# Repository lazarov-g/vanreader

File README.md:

# vanreader
Van Protocol reader 
The source is for atmega328p ( arduino chip), and it's compiled in Atmel Studio ( IDE for atmel products).

These project purpouse is to connect existing Stalk controler on Peugeot 206 with Pioneer headunit, by listening the messages on the VAN network and sending signals to player.

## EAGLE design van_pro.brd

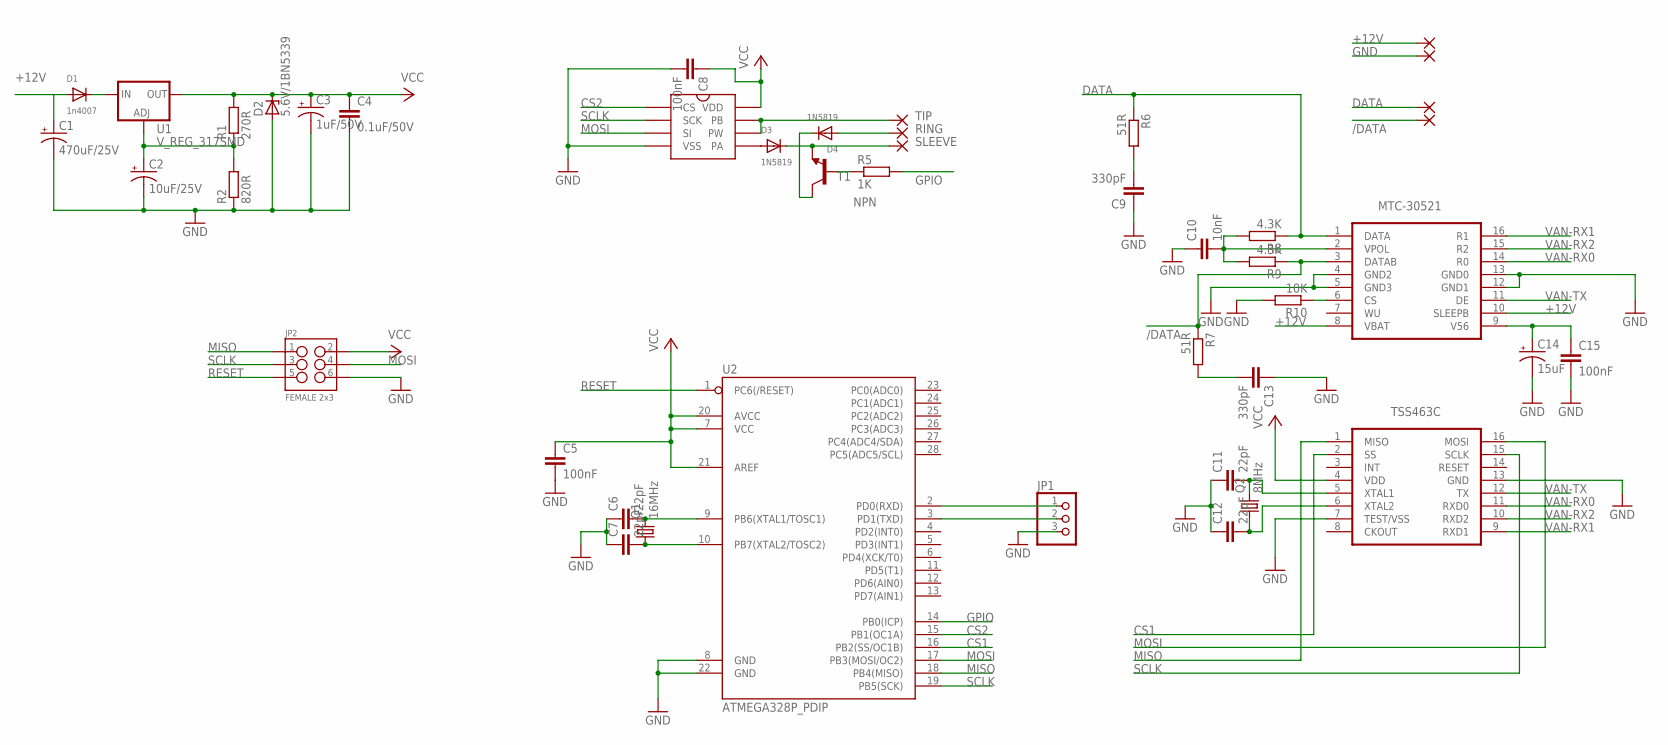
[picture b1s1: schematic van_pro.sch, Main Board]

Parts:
12V: WIREPAD2,54/0,8; 2,54/0,8
/DATA: WIREPAD2,54/0,8; 2,54/0,8
C1: 470uF/25V; E3,5-8
C2: 10uF/25V; E2-5
C3: 1uF/50V; E2-5
C4: 0.1uF/50V; C0805
C5, C8: 100nF; C0603
C6, C7, C11, C12: 22pF; C0603; MPN 08052A220JAT2A
C9, C13: 330pF; C0603; MPN 08052A220JAT2A
C10: 10nF; C0603; MPN 08052A220JAT2A
C14: 15uF; EIA3216; MPN 08052A220JAT2A
C15: 100nF; C1206; MPN 08052A220JAT2A
D1: 1n4007; SMADIODE
D2: 5.6V/1BN5339; DO41Z10
D3, D4: 1N5819; SMADIODE
DATA: WIREPAD2,54/0,8; 2,54/0,8
GND: WIREPAD2,54/0,8; 2,54/0,8
IC1: MCP41100; SO8
IC2: MTC-20521; MTC-30521
JP1: PINHD-1X3; 1X03
JP2: FEMALE 2x3; 2X3
Q1: 16MHz; HC49UP; MPN HC49SM-3.6864-30-50-60-16-ATF
Q2: 8MHz; HC49UP; MPN HC49SM-3.6864-30-50-60-16-ATF
R1: 270R; R0805
R2: 820R; R0805
R5: 1K; R0603
R6, R7: 51R; R0603
R8, R9: 4.3K; R0603
R10: 10K; R0603
RNG: 1,6/0,8
SL: 1,6/0,8
T1: NPN; SOT23-EBC
TIP: 1,6/0,8
U1: V_REG_317SMD; SOT223
U2: ATMEGA328P_PDIP; DIL28-3
VAN1: TSS463C

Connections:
+12V: 12V.1, C1.+, D1.A, IC2.8 (VBAT), IC2.10 (SLEEPB)
/DATA: /DATA.1, IC2.3 (DATAB), R7.1, R9.1
CS1: U2.16 (PB2(SS/OC1B)), VAN1.2 (SS)
CS2: IC1.1 (CS), U2.15 (PB1(OC1A))
DATA: DATA.1, IC2.1 (DATA), R6.1, R8.1
GND: C1.-, C2.-, C3.-, C4.2, C5.2, C6.1, C7.1, C8.2, C9.1, C10.1, C11.1, C12.1, C13.1, C14.C (-), C15.2, D2.A, GND.1, IC1.4 (VSS), IC2.4 (GND2), IC2.5 (GND3), IC2.12 (GND1), IC2.13 (GND0), JP1.3, JP2.6, R2.1, R10.2, U2.8 (GND), U2.22 (GND), VAN1.7 (TEST/VSS), VAN1.13 (GND)
GPIO: R5.2, U2.14 (PB0(ICP))
MISO: JP2.1, U2.18 (PB4(MISO)), VAN1.1 (MISO)
MOSI: IC1.3 (SI), JP2.4, U2.17 (PB3(MOSI/OC2)), VAN1.16 (MOSI)
unnamed: C11.2, Q2.2, VAN1.5 (XTAL1)
unnamed: D3.A, IC1.5 (PA)
unnamed: D4.C, T1.C
unnamed: C6.2, Q1.2, U2.9 (PB6(XTAL1/TOSC1))
unnamed: C7.2, Q1.1, U2.10 (PB7(XTAL2/TOSC2))
unnamed: R5.1, T1.B
unnamed: C12.2, Q2.1, VAN1.6 (XTAL2)
unnamed: C2.+, R1.1, R2.2, U1.1 (ADJ)
unnamed: D1.C, U1.3 (IN)
unnamed: IC2.6 (CS), R10.1
unnamed: C10.2, IC2.2 (VPOL), R8.2, R9.2
unnamed: C13.2, R7.2
unnamed: C9.2, R6.2
unnamed: C14.A (+), C15.1, IC2.9 (V56)
RESET: JP2.5, U2.1 (PC6(/RESET))
RING: D4.A, RNG.1
RX: JP1.1, U2.2 (PD0(RXD))
SCLK: IC1.2 (SCK), JP2.3, U2.19 (PB5(SCK)), VAN1.15 (SCLK)
SLEEVE: D3.C, SL.1, T1.E
TIP: IC1.6 (PW), IC1.7 (PB), TIP.1
TX: JP1.2, U2.3 (PD1(TXD))
VAN-RX0: IC2.14 (R0), VAN1.11 (RXD0)
VAN-RX1: IC2.16 (R1), VAN1.9 (RXD1)
VAN-RX2: IC2.15 (R2), VAN1.10 (RXD2)
VAN-TX: IC2.11 (DE), VAN1.12 (TX)
VCC: C3.+, C4.1, C5.1, C8.1, D2.C, IC1.8 (VDD), JP2.2, R1.2, U1.2 (OUT), U2.7 (VCC), U2.20 (AVCC), U2.21 (AREF), VAN1.4 (VDD)

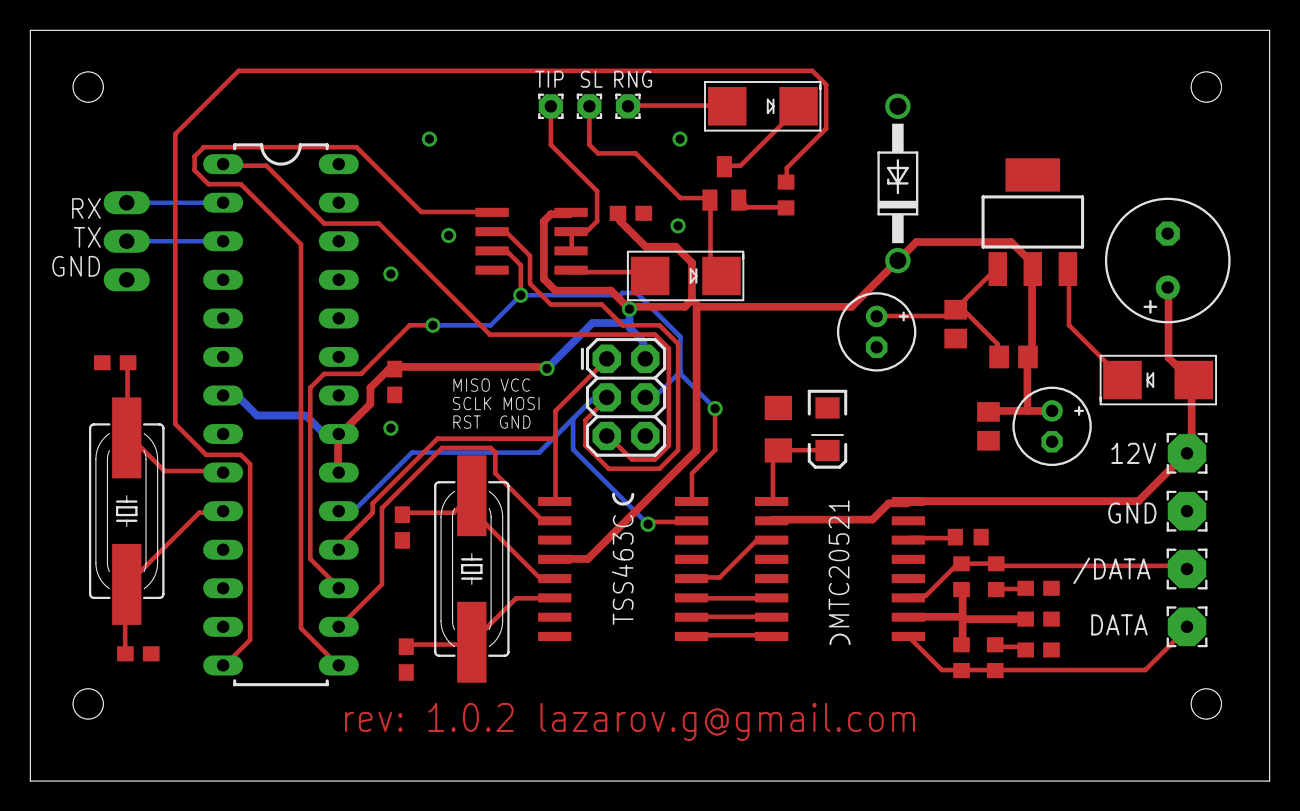
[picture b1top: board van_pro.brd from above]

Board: 2 copper layers, 81.6 x 49.5 mm, 44 parts (1 on the bottom side), 35 nets.

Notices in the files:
parts and their libraries:
SparkFun-Capacitors: Licensing: Creative Commons ShareAlike 4.0 International - https://creativecommons.org/licenses/by-sa/4.0
